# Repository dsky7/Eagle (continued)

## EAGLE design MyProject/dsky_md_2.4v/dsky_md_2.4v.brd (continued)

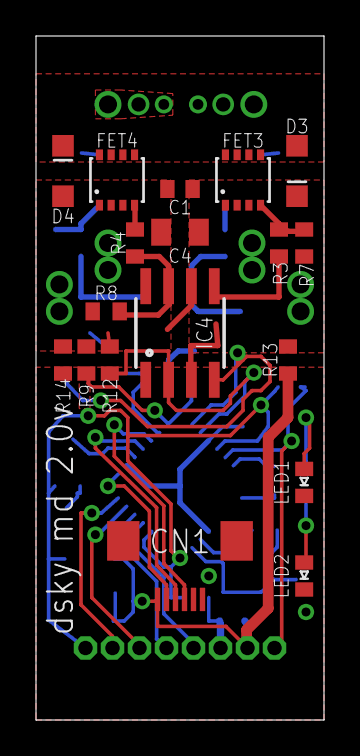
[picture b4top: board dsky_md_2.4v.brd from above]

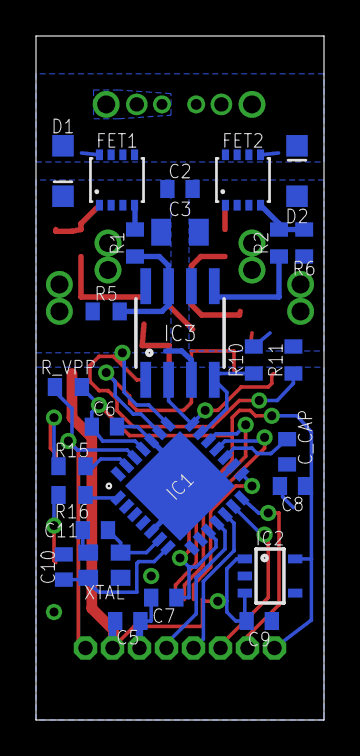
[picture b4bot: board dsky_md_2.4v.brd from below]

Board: 2 copper layers, 16.0 x 38.0 mm, 46 parts (27 on the bottom side), 34 nets.

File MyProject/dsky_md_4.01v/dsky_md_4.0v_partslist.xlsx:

dsky md 4.0v パーツリスト
パーツ | Value | Package | Shop | 商品名ショウヒンメイ | 通販コード（RS品番） | メーカー | １枚当たりの必要数マイアヒツヨウスウ | 備考ビコウ
C1 | 0.1uF | 1608 | akizuki | チップ積層セラミックコンデンサー０．１μＦ５０Ｖ １６０８ （２００個入） | P-04940 | 株式会社村田製作所 | 1
C2 | 0.1uF | 1608 | akizuki | チップ積層セラミックコンデンサー０．１μＦ５０Ｖ １６０８ （２００個入） | P-04940 | 株式会社村田製作所 | 1
C3 | 4.7uF | 2012 | akizuki | チップ積層セラミックコンデンサー ４．７μＦ５０Ｖ ２０１２ （２０個入） | P-07548 | Samsung Electronics Co., Ltd. | 1
C4 | 4.7uF | 2012 | akizuki | チップ積層セラミックコンデンサー ４．７μＦ５０Ｖ ２０１２ （２０個入） | P-07548 | Samsung Electronics Co., Ltd. | 1
C5 | 0.1uF | 1608 | akizuki | チップ積層セラミックコンデンサー０．１μＦ５０Ｖ １６０８ （２００個入） | P-04940 | 株式会社村田製作所 | 1
C6 | 0.1uF | 1608 | akizuki | チップ積層セラミックコンデンサー０．１μＦ５０Ｖ １６０８ （２００個入） | P-04940 | 株式会社村田製作所 | 1
C7 | 0.1uF | 1608 | akizuki | チップ積層セラミックコンデンサー０．１μＦ５０Ｖ １６０８ （２００個入） | P-04940 | 株式会社村田製作所 | 1
C8 | 1uF | 1608 | akizuki | チップ積層セラミックコンデンサー１μＦ１６Ｖ １６０８ １００個入 | P-02996 | 株式会社村田製作所 | 1
C9 | 0.1uF | 1608 | akizuki | チップ積層セラミックコンデンサー０．１μＦ５０Ｖ １６０８ （２００個入） | P-04940 | 株式会社村田製作所 | 1
C10 | 18pF | 1608 | akizuki | チップ積層セラミックコンデンサー １８ｐＦ５０Ｖ （１００個入） | P-05523 | 株式会社村田製作所 | 1
C11 | 18pF | 1608 | akizuki | チップ積層セラミックコンデンサー １８ｐＦ５０Ｖ （１００個入） | P-05523 | 株式会社村田製作所 | 1
C12 | 10uF | 1608 | akizuki | チップ積層セラミックコンデンサー １０μＦ２５Ｖ （１０個入） | P-07768 | 株式会社村田製作所 | 1
CN1 | B5B-ZR-SM4-TF | ZH5_SMT | Digi-Key | B5B-ZR-SM4-TF (LF)(SN)(P) | 455-1684-1-ND | 日本圧着端子製造(JST) | 1
CN2 | B06B-PASK | JST-PA6 | Digi-Key | B06B-PASK(LF)(SN) | 455-1821-ND | 日本圧着端子製造(JST) | 1
CN3 | B2B-ZR | B2B-ZR | RS | コネクタ,ナイロン製,ヘッダーハウジング,B2B-ZR (LF)(SN),ベース付ピン,トップ型,2極 | 546-9230 | 日本圧着端子製造(JST) | 1
D1 | SS2040 | SOD-123FL | akizuki | 表面実装用ショットキーバリアダイオード（４０Ｖ２Ａ）ＳＳ２０４０ＦＬ（２０個入） | I-02073 | PANJIT INTERNATIONAL INC | 1
D2 | SS2040 | SOD-123FL | akizuki | 表面実装用ショットキーバリアダイオード（４０Ｖ２Ａ）ＳＳ２０４０ＦＬ（２０個入） | I-02073 | PANJIT INTERNATIONAL INC | 1
D3 | SS2040 | SOD-123FL | akizuki | 表面実装用ショットキーバリアダイオード（４０Ｖ２Ａ）ＳＳ２０４０ＦＬ（２０個入） | I-02073 | PANJIT INTERNATIONAL INC | 1
D4 | SS2040 | SOD-123FL | akizuki | 表面実装用ショットキーバリアダイオード（４０Ｖ２Ａ）ＳＳ２０４０ＦＬ（２０個入） | I-02073 | PANJIT INTERNATIONAL INC | 1
FET1 | ECH8310 | ECH8 | RS | ＜New＞MOSFETトランジスタ | 791-9421 | ON Semiconductor | 1
FET2 | ECH8419 | ECH8 | RS | ＜New＞MOSFETトランジスタ | 802-0813 | ON Semiconductor | 1
FET3 | ECH8310 | ECH8 | RS | ＜New＞MOSFETトランジスタ | 791-9421 | ON Semiconductor | 1
FET4 | ECH8419 | ECH8 | RS | ＜New＞MOSFETトランジスタ | 802-0813 | ON Semiconductor | 1
IC1 | DSPIC33EP32MC202 | QFN-S28 | 購入済みコウニュウズ |  |  |  | 1
IC2 | NJM2866F33 | SSOP5-P-0.95 | akizuki | 低損失表面実装型レギュレータ ３．３Ｖ１００ｍＡ ＮＪＭ２８６６Ｆ３３ １０個入 | I-05448 | 新日本無線株式会社 | 1
IC3 | LM5111-1M/NOPB | SOIC8 | RS | LM5111-1M, MOSFETドライバ 5A 2-Channel, 非反転, 3.5 to 14V, 8-Pin, SOIC N | 504-5553 | Texas Instruments | 1
IC4 | LM5111-1M/NOPB | SOIC8 | RS | LM5111-1M, MOSFETドライバ 5A 2-Channel, 非反転, 3.5 to 14V, 8-Pin, SOIC N | 504-5553 | Texas Instruments | 1
LED1 | 1608 | 1608 | akizuki | 青色チップＬＥＤ ＯＳＢＬ１６０８ ２３ｍｃｄ（２０個入） | I-03982 | OptoSupply | 1
LED2 | 1608 | 1608 | akizuki | 赤色チップＬＥＤ ＯＳＨＲ１６０８ ３５ｍｃｄ （２０個入） | I-03978 | OptoSupply | 1
R1 | 10 | 1608 | 在庫確認お願いしますザイコカクニンネガ |  |  |  | 1
R2 | 10 | 1608 | 在庫確認お願いしますザイコカクニンネガ |  |  |  | 1
R3 | 10 | 1608 | 在庫確認お願いしますザイコカクニンネガ |  |  |  | 1
R4 | 10 | 1608 | 在庫確認お願いしますザイコカクニンネガ |  |  |  | 1
R5 | 10K | 1608 | 在庫ありザイコ |  |  |  | 1
R6 | 10K | 1608 | 在庫ありザイコ |  |  |  | 1
R7 | 10K | 1608 | 在庫ありザイコ |  |  |  | 1
R8 | 10K | 1608 | 在庫ありザイコ |  |  |  | 1
R9 | 10K | 1608 | 在庫ありザイコ |  |  |  | 1
R10 | 10K | 1608 | 在庫ありザイコ |  |  |  | 1
R11 | 10K | 1608 | 在庫ありザイコ |  |  |  | 1
R12 | 10K | 1608 | 在庫ありザイコ |  |  |  | 1
R13 | 0 | 1608 | RS | 抵抗器,厚膜,角型チップ,ERJ3GEY0R00V,Size1608,定格電流1A | 433-425 | Panasonic | 1
R14 | 0 | 1608 | RS | 抵抗器,厚膜,角型チップ,ERJ3GEY0R00V,Size1608,定格電流1A | 433-425 | Panasonic | 1
R15 | 200 | 1608 | 在庫ありザイコ |  |  |  | 1
R16 | 470 | 1608 | 在庫ありザイコ |  |  |  | 1
R17 | 0 | 1005 | RS | チップ抵抗器,薄膜,CRG0402ZR,Size1005,0.063W,0Ω,1%,1% | 667-8520 | TE Connectivity | 1
R18 | 0 | 1005 | RS | チップ抵抗器,薄膜,CRG0402ZR,Size1005,0.063W,0Ω,1%,1% | 667-8520 | TE Connectivity | 1
R19 | 10k | 1608 | 在庫ありザイコ |  |  |  | 1
XTAL | X22 | SMD_X22 | akizuki | 表面実装型クリスタル（水晶発振子） ＦＡ２３８－２０ＭＨｚ （４個入） | P-02458 | エプソントヨコム株式会社 | 1
配線に用いるパーツハイセンモチ
配線ハイセン | ケーブル | AWG28 | RS | Speedbloc 10 Way 非遮蔽 フラットケーブル, 12.7mm Width | 289-9846 | Speedbloc | 5ｍ
配線ハイセン | ケーブル | AWG26 | RS | 3M 14 Way 非遮蔽 フラットケーブル, 17.78mm Width | 382-153 | 3M | 30m
ハウジング | ZHR-2 | ZH | RS | コネクタ,ナイロン製,リセプタクルハウジング,ZHR-2,ハウジング,2極 | 373-4419 | 日本圧着端子製造(JST) | 20
ハウジング | ZHR-5 | ZH | RS | コネクタ,ナイロン製,リセプタクルハウジング,ZHR-5,ハウジング,5極 | 373-4453 | 日本圧着端子製造(JST) | 20
コンタクト | SZH-002T-P0.5 | ZH | RS | コネクタ,ナイロン製,電線用,コンタクト,SZH-002T-P0.5,コンタクト,AWG28/26 | 373-4188 | 日本圧着端子製造(JST) | 100
コンタクト | SZH-003T-P0.5 | ZH | RS | ZH 1.5mm CONTACT 32-28 AWG | 762-0768 | 日本圧着端子製造(JST) | 100
コンタクト | BZH-002T-P0.5 | ZH | RS | ZH 1.5mm CONTACT 28-26 AWG LOOSE | 762-0759 | 日本圧着端子製造(JST) | 100
コンタクト | BZH-003T-P0.5 | ZH | RS | ZH 1.5MM CONTACT 32-28 AWG LOOSE | 762-0761 | 日本圧着端子製造(JST) | 100
ハウジング | PAP-06V-S | PA | RS | コネクタ,ナイロン,PA,ハウジング,PAP-06V-S,6極 | 476-6805 | 日本圧着端子製造(JST) | 20
コンタクト | SPHD-001T-P0.5 | PA | RS | 圧着端子,メス,PHDシリーズ,SPHD-001T-P0.5,AWG26-22 | 688-1381 | 日本圧着端子製造(JST) | 100
コンタクト | SPHD-002T-P0.5 | PA | RS | 圧着端子,メス,PHDシリーズ,SPHD-002T-P0.5,AWG28-24 | 688-1385 | 日本圧着端子製造(JST) | 100
コンタクト | BPHD-001T-P0.5 | PA | RS | コネクタ,ナイロン,PA,コンタクト,BPHD-001T-P0.5,0.13to0.33mmsq用 | 476-6748 | 日本圧着端子製造(JST) | 100

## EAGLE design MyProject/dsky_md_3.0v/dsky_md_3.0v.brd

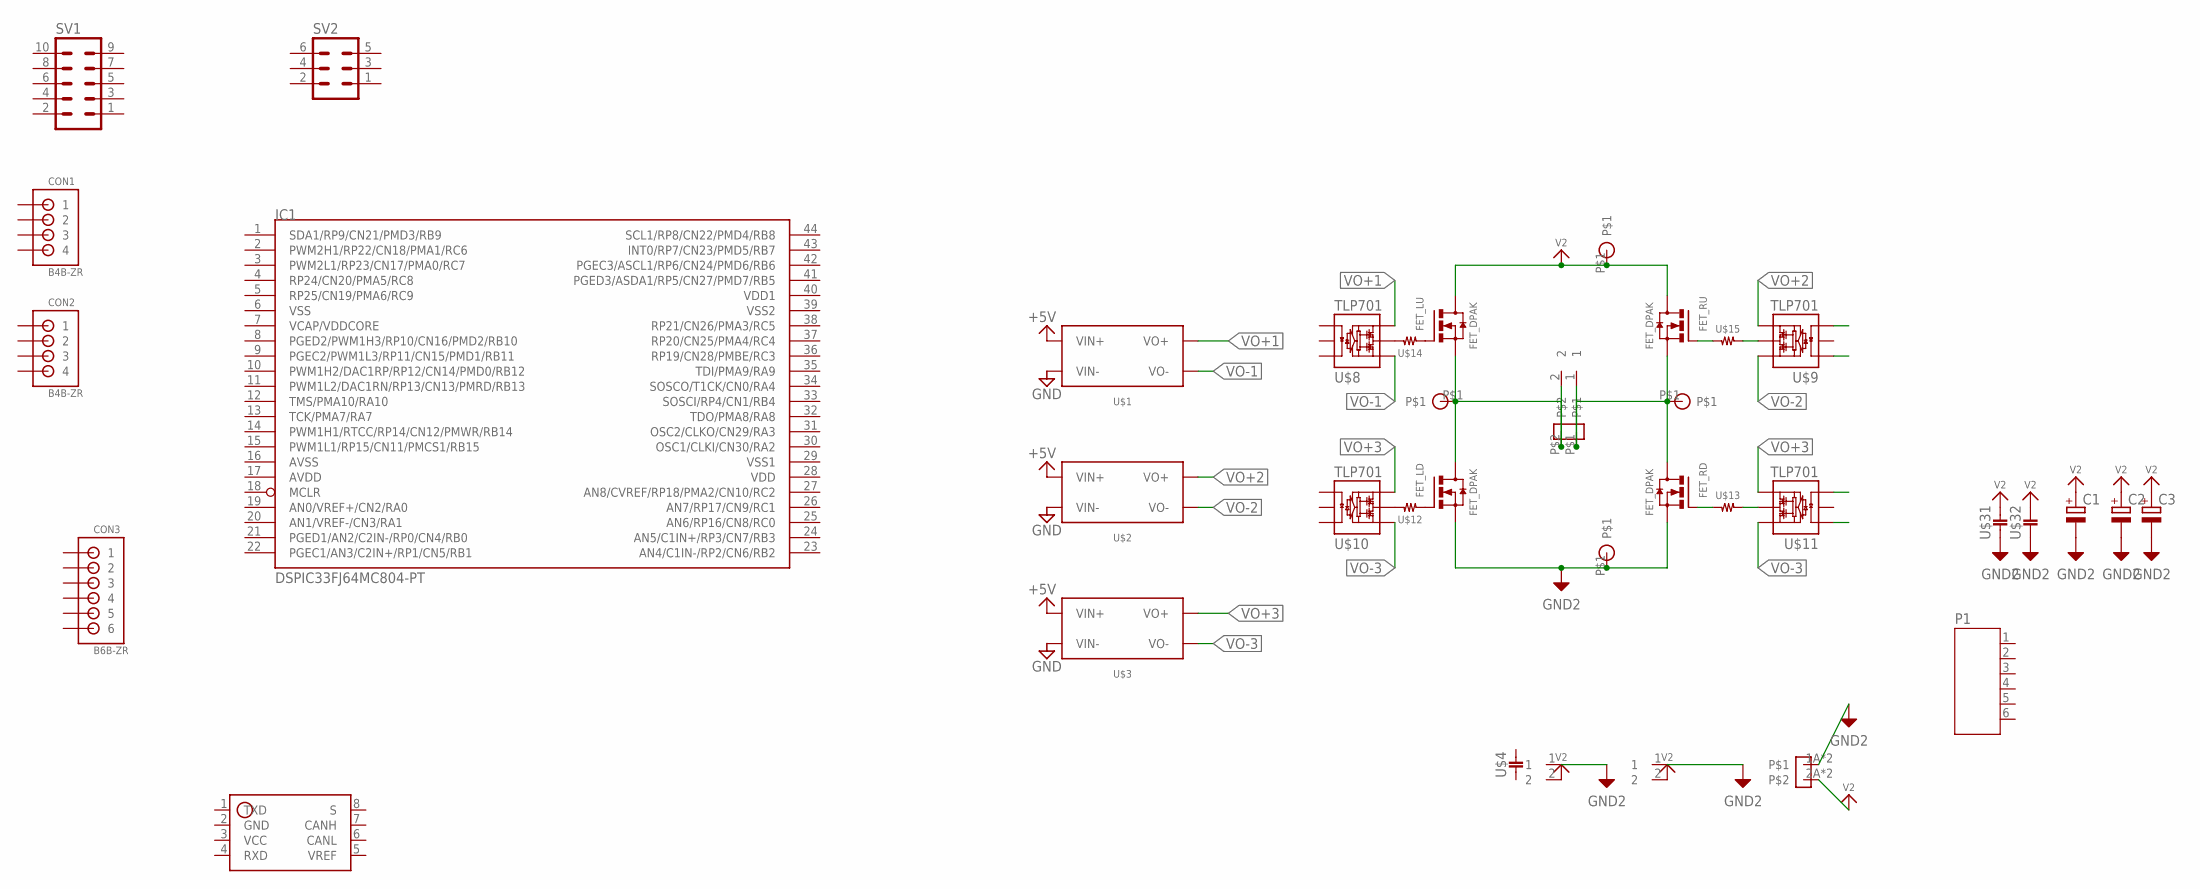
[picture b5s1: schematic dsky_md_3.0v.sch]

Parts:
C1, C2: CPOL-EUE3.5-8; E3,5-8
C3: CPOL-EU150CLZ-1010; 150CLZ-1010
CON1, CON2: B4B-ZR
CON3: B6B-ZR
FET_LD: FET_DPAK; DPAK
FET_LU: FET_DPAK; DPAK
FET_RD: FET_DPAK; DPAK
FET_RU: FET_DPAK; DPAK
IC1: DSPIC33FJ64MC804-PT; TQFP44
P1: JST-PH6
SV1: ML10
SV2: ML6
U$1, U$2, U$3: MAU100; MAU
U$4: 1608
U$5, U$16, U$23: VL_2
U$8, U$9, U$10, U$11: TLP701; 11-5J1
U$12, U$13, U$14, U$15: RESISTOR__SMD; 1608
U$21, U$22, U$43, U$44: HAN_FAST; HOLE_4.4MM
U$24: TERMINAL_2P
U$31, U$32: 3225
U$45: SN65HVD1050; SOIC8
U$46: ML_300_2P

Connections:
+5V: U$1.P$1 (VIN+), U$2.P$1 (VIN+), U$3.P$1 (VIN+)
AVDD: IC1.17 (AVDD)
AVSS: IC1.16 (AVSS)
GND: U$1.P$2 (VIN-), U$2.P$2 (VIN-), U$3.P$2 (VIN-)
GND2: C1.-, C2.-, C3.-, FET_LD.3 (S), FET_RD.3 (S), U$5.1, U$16.1, U$31.P$2 (2), U$32.P$2 (2), U$43.P$1, U$46.1A, U$46.1B
M1: FET_LD.2 (D), FET_LU.3 (S), U$21.P$1, U$23.2, U$24.P$2
M2: FET_RD.2 (D), FET_RU.3 (S), U$22.P$1, U$23.1, U$24.P$1
unnamed: U$10.5 (OUT), U$12.2
unnamed: FET_LU.1 (G), U$14.1
unnamed: FET_LD.1 (G), U$12.1
unnamed: FET_RD.1 (G), U$13.1
unnamed: U$11.5 (OUT), U$13.2
unnamed: U$8.5 (OUT), U$14.2
unnamed: FET_RU.1 (G), U$15.1
unnamed: U$9.5 (OUT), U$15.2
V2: C1.+, C2.+, C3.+, FET_LU.2 (D), FET_RU.2 (D), U$5.2, U$16.2, U$31.P$1 (1), U$32.P$1 (1), U$44.P$1, U$46.2A, U$46.2B
VDD: IC1.28 (VDD)
VDD1: IC1.40 (VDD1)
VO+1: U$1.P$5 (VO+), U$8.6 (VCC)
VO+2: U$2.P$5 (VO+), U$9.6 (VCC)
VO+3: U$3.P$5 (VO+), U$10.6 (VCC), U$11.6 (VCC)
VO-1: U$1.P$3 (VO-), U$8.4 (GND)
VO-2: U$2.P$3 (VO-), U$9.4 (GND)
VO-3: U$3.P$3 (VO-), U$10.4 (GND), U$11.4 (GND)
VSS: IC1.6 (VSS)
VSS1: IC1.29 (VSS1)
VSS2: IC1.39 (VSS2)

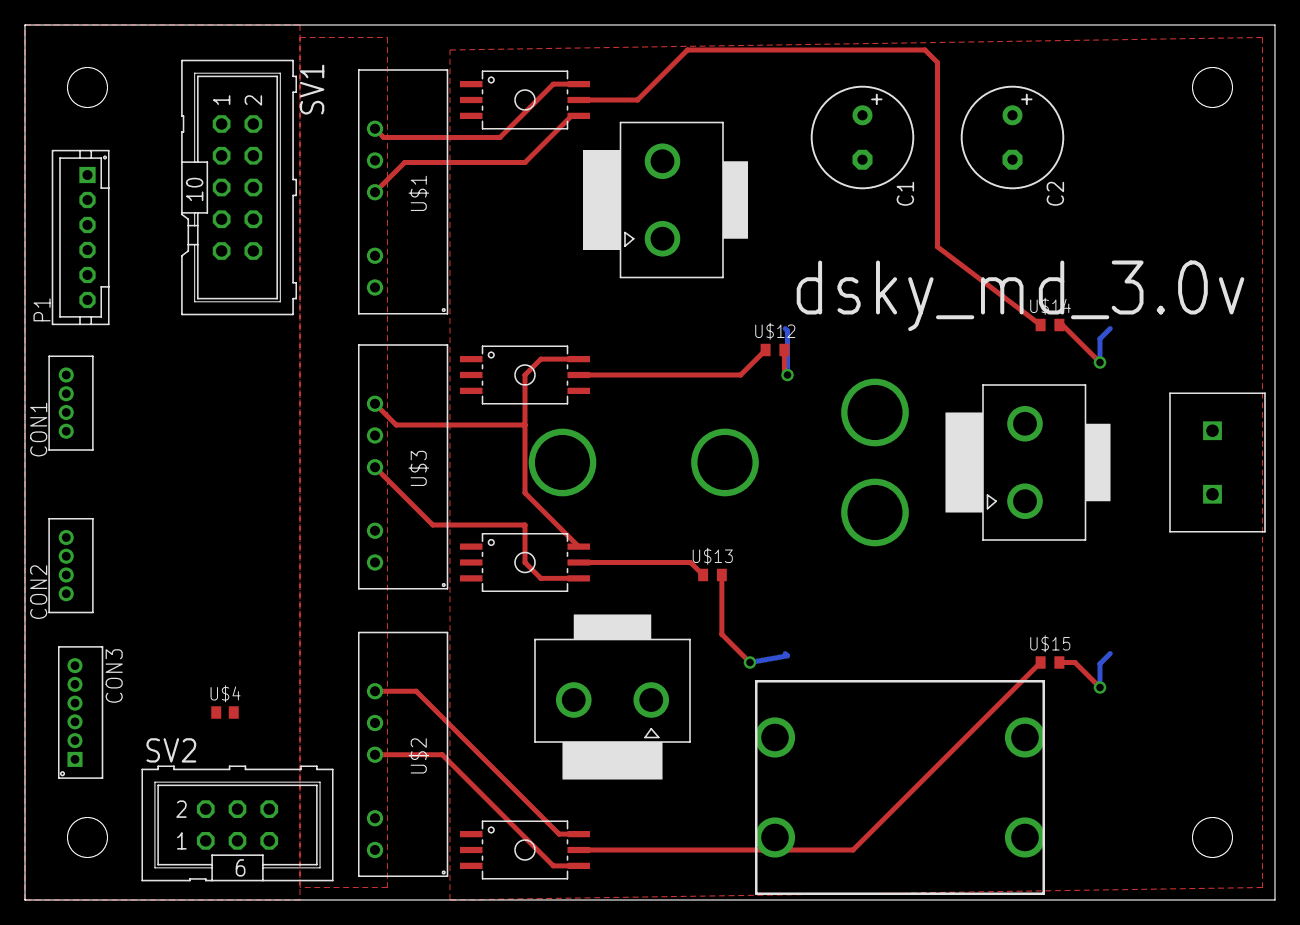
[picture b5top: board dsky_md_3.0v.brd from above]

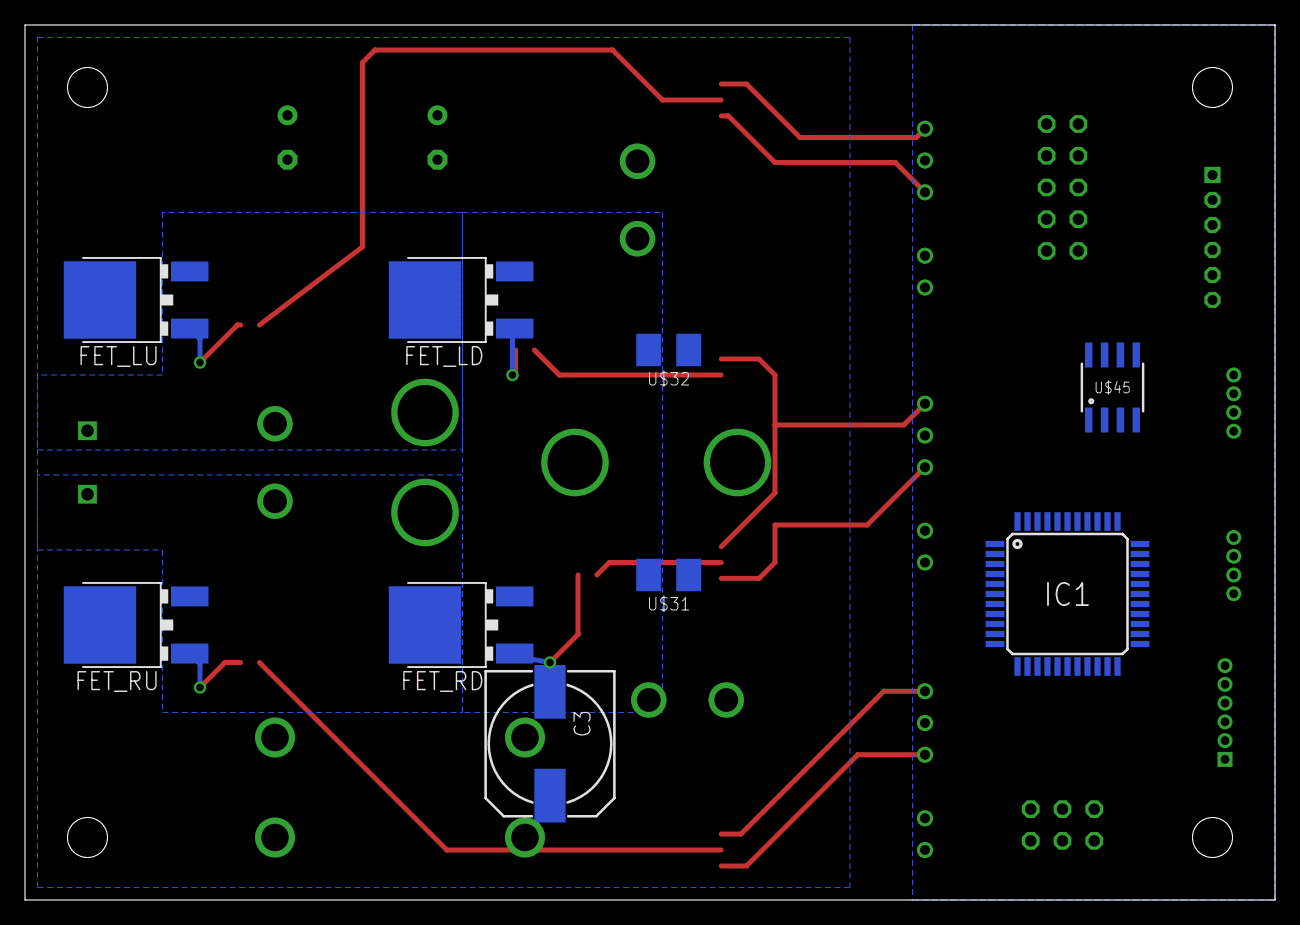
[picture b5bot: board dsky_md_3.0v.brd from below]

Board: 2 copper layers, 100.0 x 70.0 mm, 38 parts (9 on the bottom side), 20 nets.

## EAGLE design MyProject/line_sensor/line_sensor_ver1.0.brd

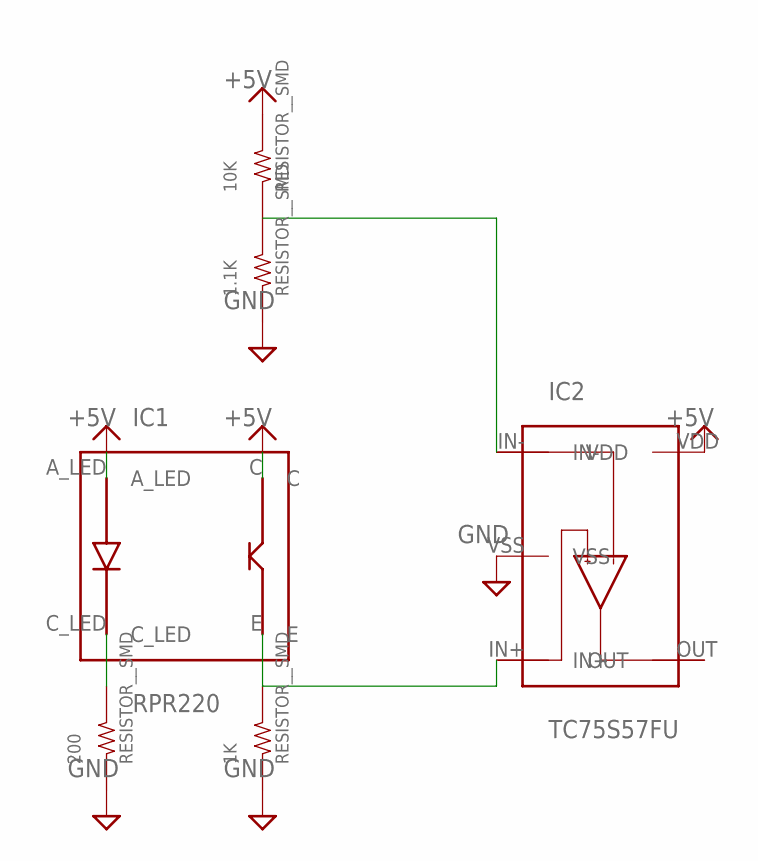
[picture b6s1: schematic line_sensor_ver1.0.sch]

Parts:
1.1K, 1K, 10K, 200: RESISTOR__SMD; 1608
IC1: RPR220
IC2: TC75S57FU; SSOP5-P-0.65A

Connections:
+5V: 10K.2, IC1.A_LED, IC1.C, IC2.VDD
GND: 1.1K.1, 1K.1, 200.1, IC2.VSS
unnamed: 1.1K.2, 10K.1, IC2.IN-
unnamed: 1K.2, IC1.E, IC2.IN+
unnamed: 200.2, IC1.C_LED

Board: 2 copper layers, 6 parts (5 on the bottom side), 5 nets, no tracks yet.
